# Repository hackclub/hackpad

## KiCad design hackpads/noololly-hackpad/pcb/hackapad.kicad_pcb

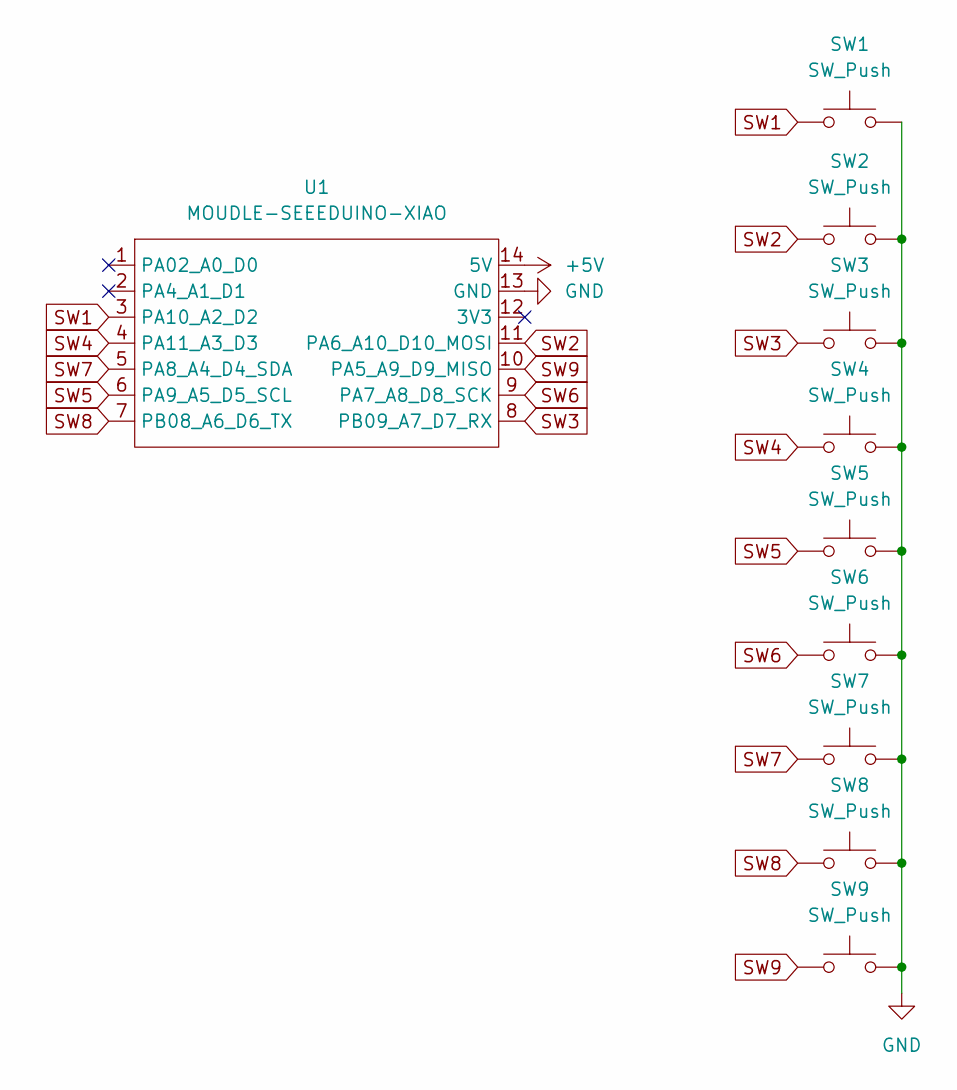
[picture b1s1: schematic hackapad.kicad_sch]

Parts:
SW1, SW2, SW3, SW4, SW5, SW6, SW7, SW8, SW9: SW_Push; SW_Cherry_MX_1.00u_PCB
U1: MOUDLE-SEEEDUINO-XIAO; XIAO-Generic-Hybrid-14P-2.54-21X17.8MM

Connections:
+5V: U1.14 (5V)
GND: SW1.2, SW2.2, SW3.2, SW4.2, SW5.2, SW6.2, SW7.2, SW8.2, SW9.2, U1.13 (GND)
SW1: SW1.1, U1.3 (PA10_A2_D2)
SW2: SW2.1, U1.11 (PA6_A10_D10_MOSI)
SW3: SW3.1, U1.8 (PB09_A7_D7_RX)
SW4: SW4.1, U1.4 (PA11_A3_D3)
SW5: SW5.1, U1.6 (PA9_A5_D5_SCL)
SW6: SW6.1, U1.9 (PA7_A8_D8_SCK)
SW7: SW7.1, U1.5 (PA8_A4_D4_SDA)
SW8: SW8.1, U1.7 (PB08_A6_D6_TX)
SW9: SW9.1, U1.10 (PA5_A9_D9_MISO)

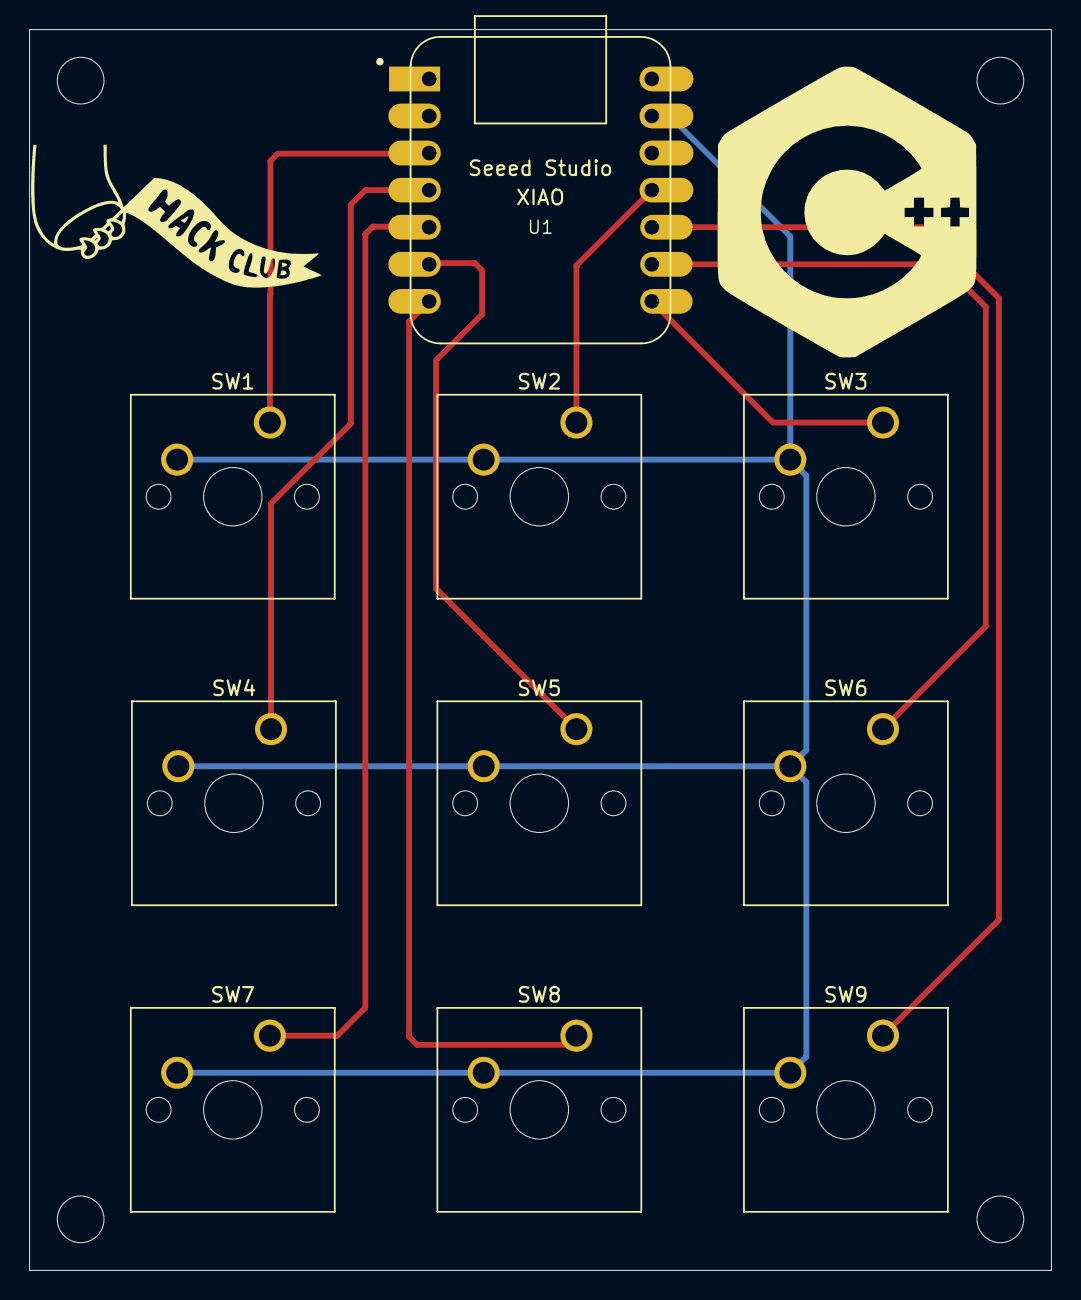
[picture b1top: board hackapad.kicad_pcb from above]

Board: 2 copper layers, 70.0 x 85.0 mm, 10 parts (0 on the bottom side), 10 nets.

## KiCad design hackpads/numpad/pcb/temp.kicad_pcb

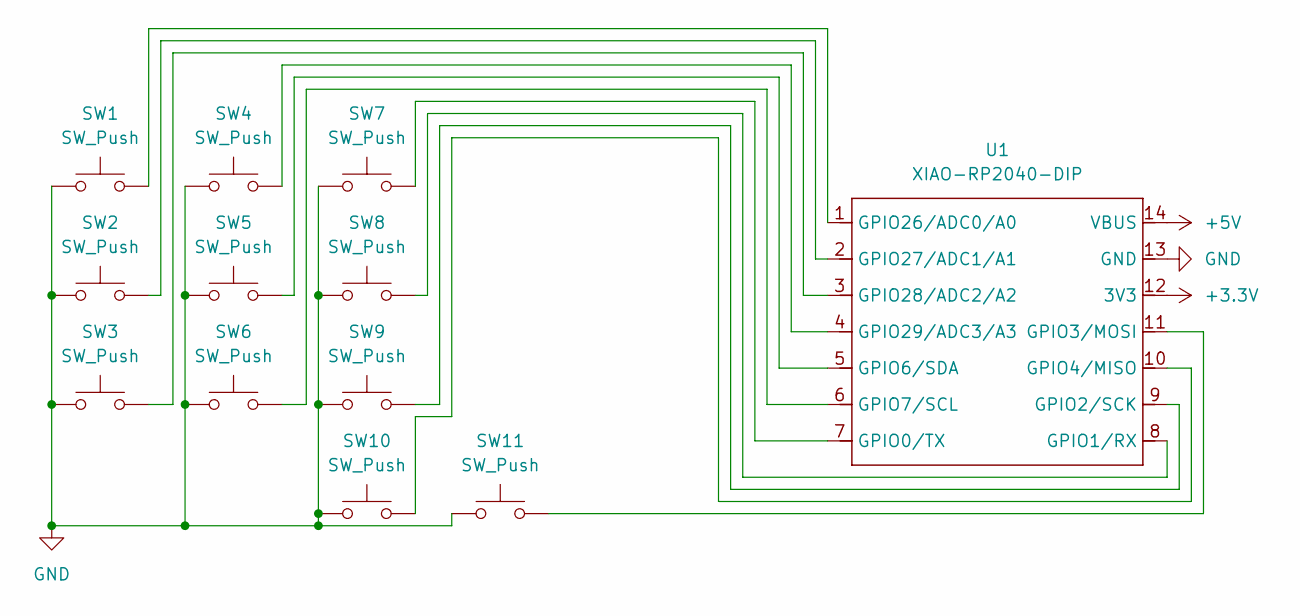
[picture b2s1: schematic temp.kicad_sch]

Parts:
SW1, SW2, SW3, SW4, SW5, SW6, SW7, SW8, SW9, SW10, SW11: SW_Push; SW_Cherry_MX_1.00u_PCB
U1: XIAO-RP2040-DIP

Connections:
+3.3V: U1.12 (3V3)
+5V: U1.14 (VBUS)
GND: SW1.1, SW2.1, SW3.1, SW4.1, SW5.1, SW6.1, SW7.1, SW8.1, SW9.1, SW10.1, SW11.1, U1.13 (GND)
unnamed: SW7.2, U1.7 (GPIO0/TX)
unnamed: SW8.2, U1.8 (GPIO1/RX)
unnamed: SW9.2, U1.9 (GPIO2/SCK)
unnamed: SW11.2, U1.11 (GPIO3/MOSI)
unnamed: SW10.2, U1.10 (GPIO4/MISO)
unnamed: SW5.2, U1.5 (GPIO6/SDA)
unnamed: SW6.2, U1.6 (GPIO7/SCL)
unnamed: SW1.2, U1.1 (GPIO26/ADC0/A0)
unnamed: SW2.2, U1.2 (GPIO27/ADC1/A1)
unnamed: SW3.2, U1.3 (GPIO28/ADC2/A2)
unnamed: SW4.2, U1.4 (GPIO29/ADC3/A3)

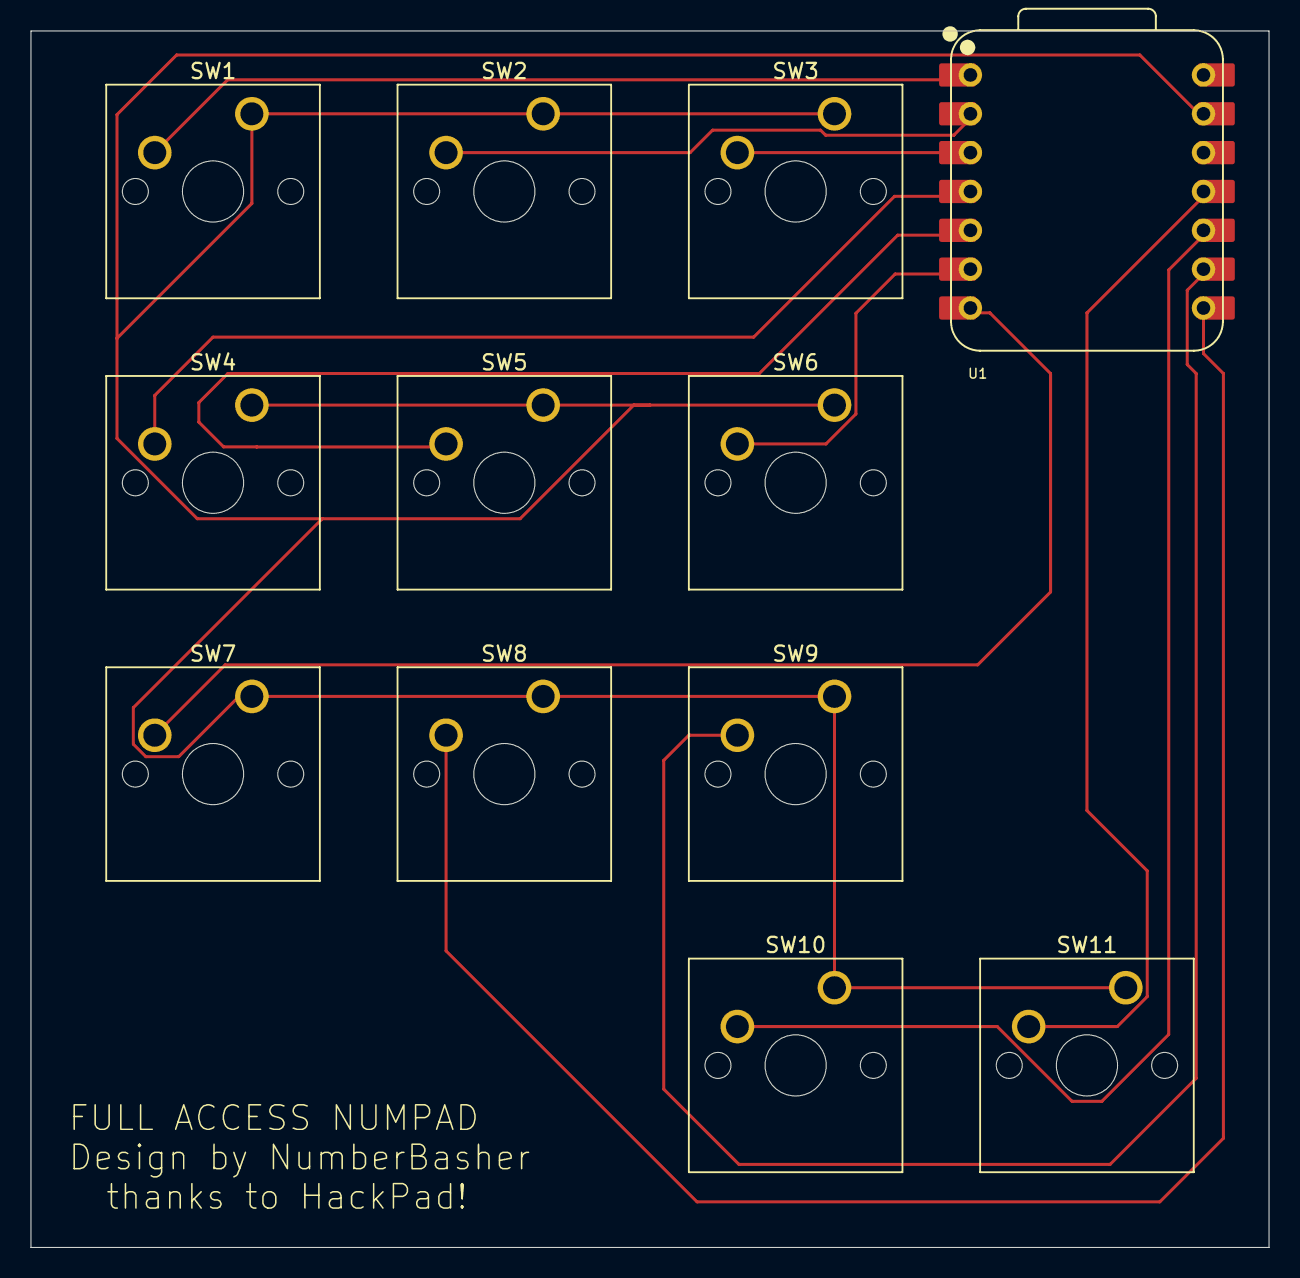
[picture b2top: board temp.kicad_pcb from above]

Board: 2 copper layers, 81.0 x 79.6 mm, 12 parts (0 on the bottom side), 12 nets.

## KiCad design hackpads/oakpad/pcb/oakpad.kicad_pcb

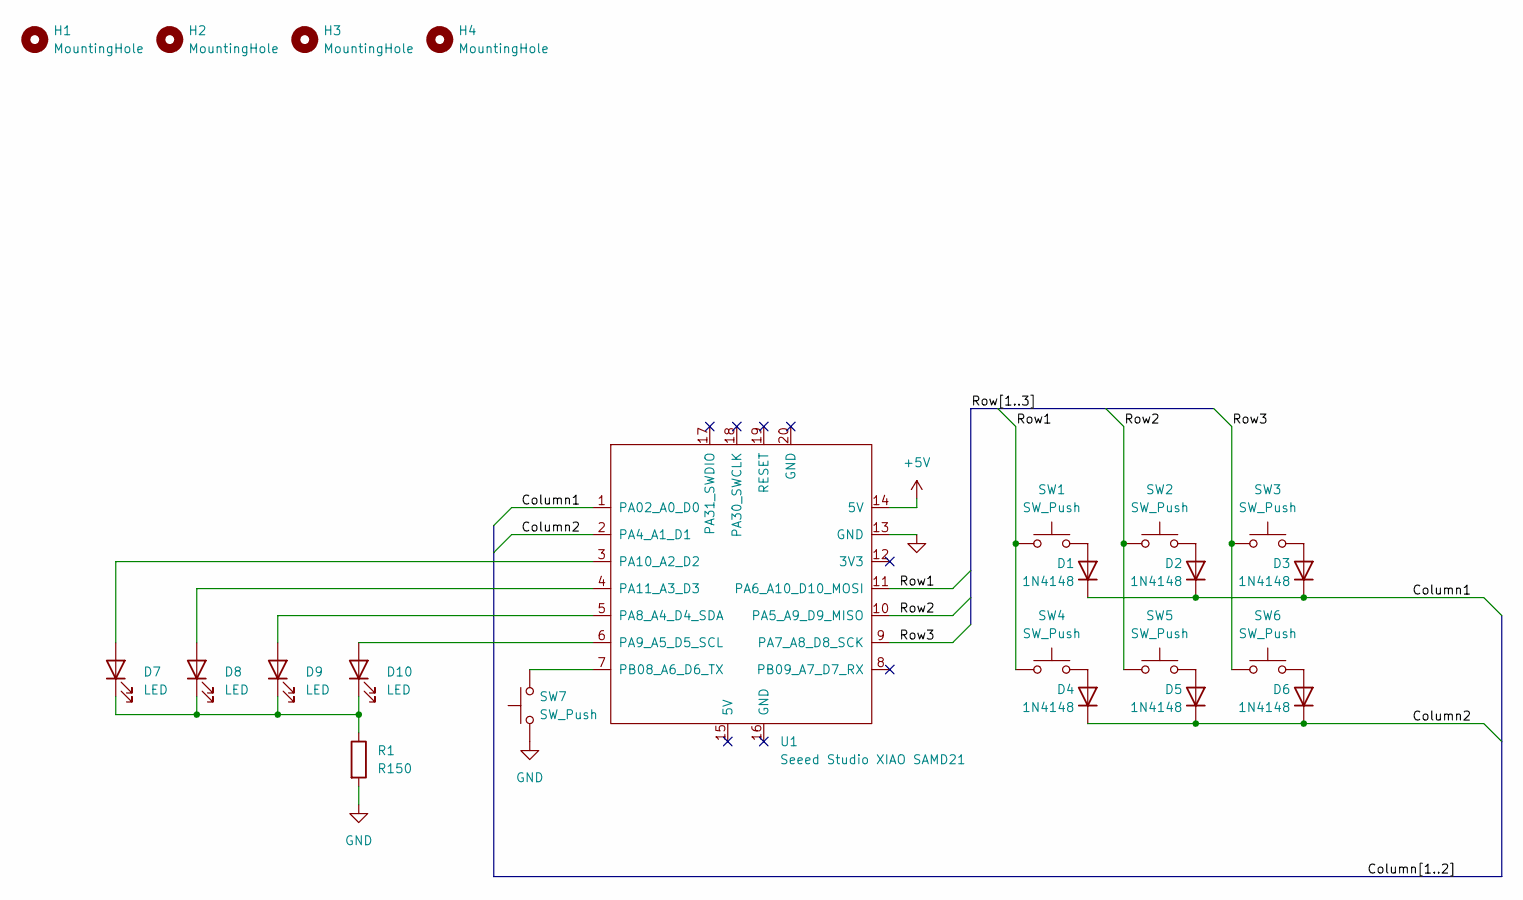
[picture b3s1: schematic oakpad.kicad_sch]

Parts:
D1, D2, D3, D4, D5, D6: 1N4148; D_DO-35_SOD27_P7.62mm_Horizontal
D7, D8, D9, D10: LED; LED_D5.0mm
H1, H2, H3, H4: MountingHole; MountingHole_3.2mm_M3
R1: R150; R_Axial_DIN0204_L3.6mm_D1.6mm_P5.08mm_Horizontal
SW1, SW2, SW3, SW4, SW5, SW6, SW7: SW_Push; SW_Cherry_MX_1.00u_PCB
U1: Seeed Studio XIAO SAMD21; XIAO-Generic-Thruhole-14P-2.54-21X17.8MM

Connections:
+5V: U1.14 (5V)
/Column1: D1.1 (K), D2.1 (K), D3.1 (K), U1.1 (PA02_A0_D0)
/Column2: D4.1 (K), D5.1 (K), D6.1 (K), U1.2 (PA4_A1_D1)
/Row1: SW1.1, SW4.1, U1.11 (PA6_A10_D10_MOSI)
/Row2: SW2.1, SW5.1, U1.10 (PA5_A9_D9_MISO)
/Row3: SW3.1, SW6.1, U1.9 (PA7_A8_D8_SCK)
GND: R1.2, SW7.1, U1.13 (GND)
unnamed: D1.2 (A), SW1.2
unnamed: D2.2 (A), SW2.2
unnamed: D3.2 (A), SW3.2
unnamed: D4.2 (A), SW4.2
unnamed: D5.2 (A), SW5.2
unnamed: D6.2 (A), SW6.2
unnamed: D7.2 (A), U1.3 (PA10_A2_D2)
unnamed: D8.2 (A), U1.4 (PA11_A3_D3)
unnamed: D9.2 (A), U1.5 (PA8_A4_D4_SDA)
unnamed: D10.2 (A), U1.6 (PA9_A5_D5_SCL)
unnamed: D7.1 (K), D8.1 (K), D9.1 (K), D10.1 (K), R1.1
unnamed: SW7.2, U1.7 (PB08_A6_D6_TX)

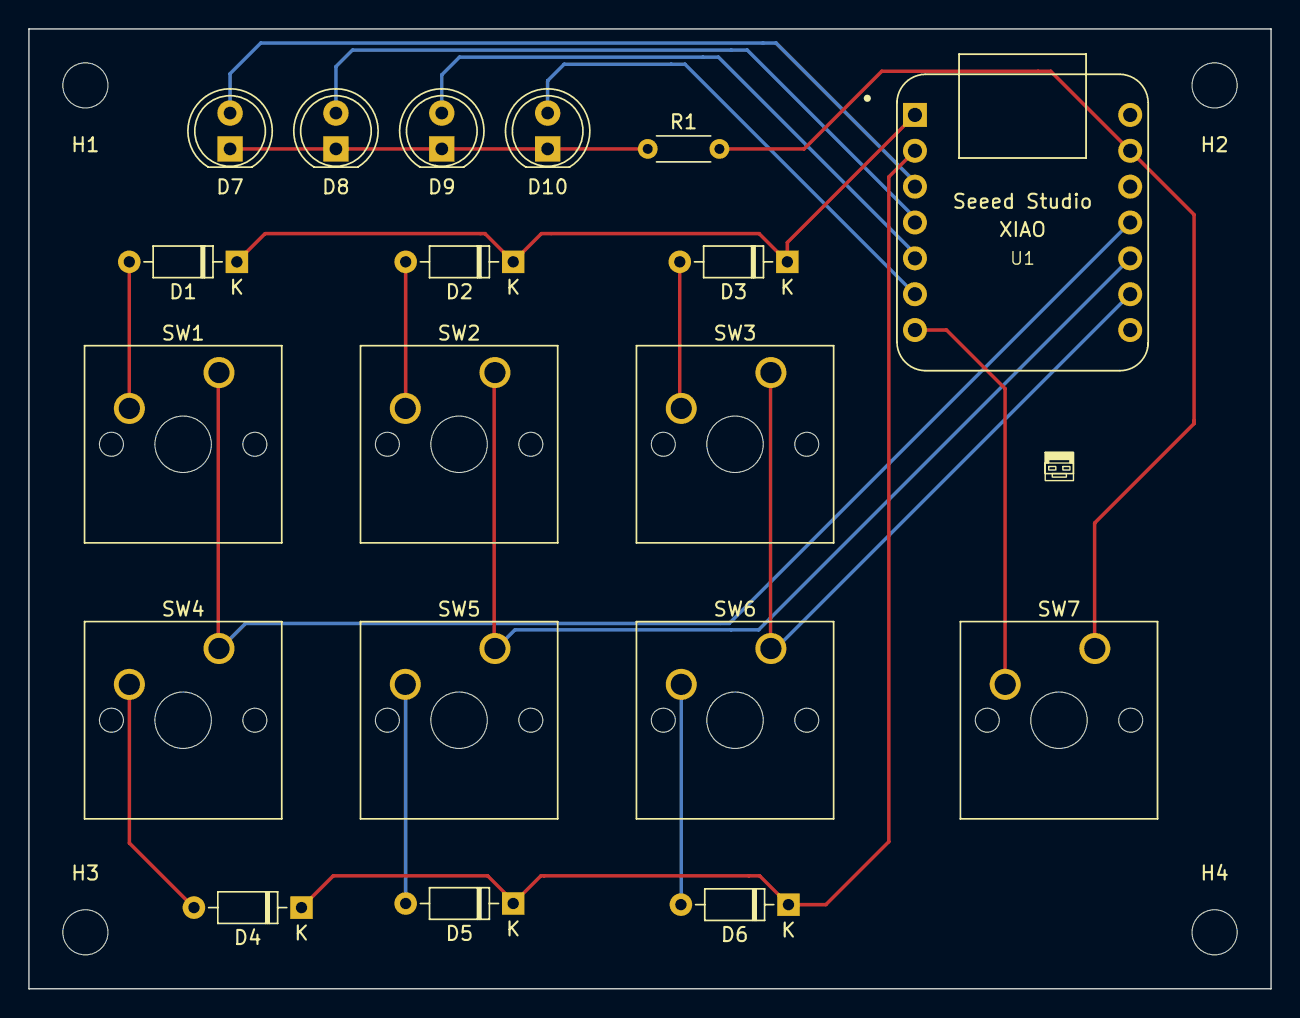
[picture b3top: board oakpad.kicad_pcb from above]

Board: 2 copper layers, 88.0 x 68.0 mm, 23 parts (0 on the bottom side), 18 nets.

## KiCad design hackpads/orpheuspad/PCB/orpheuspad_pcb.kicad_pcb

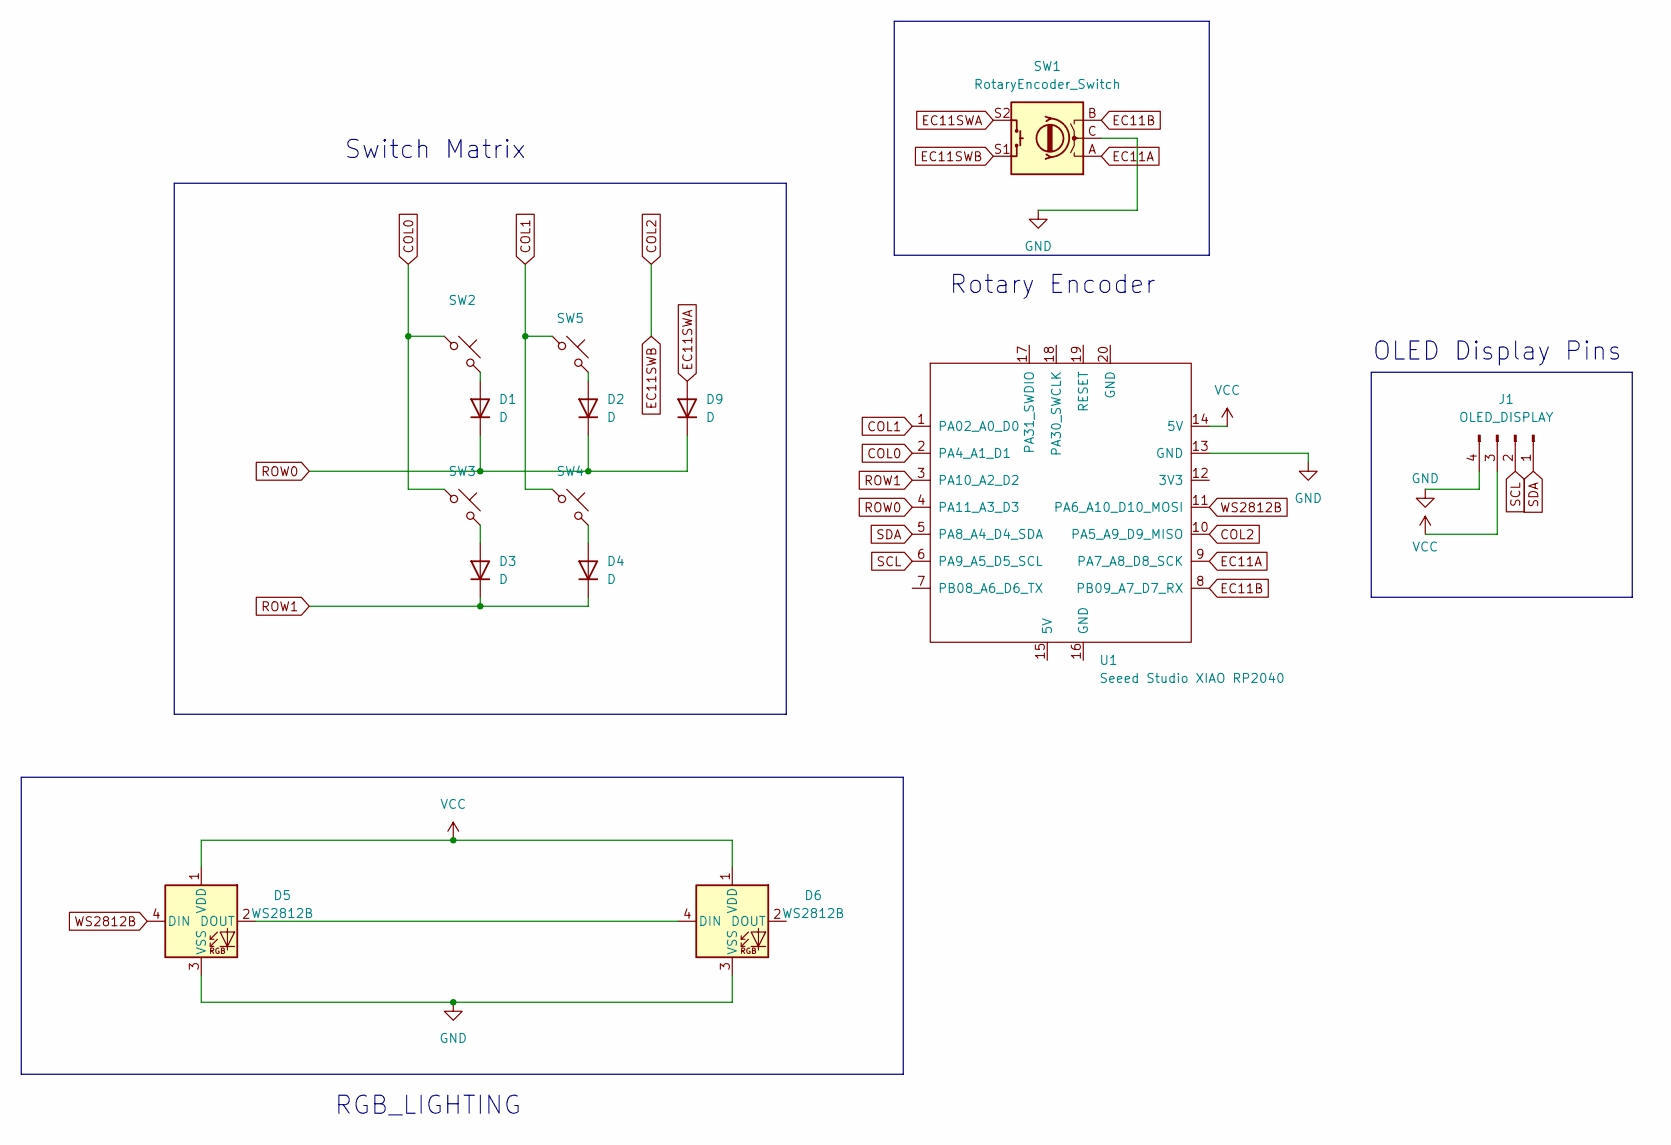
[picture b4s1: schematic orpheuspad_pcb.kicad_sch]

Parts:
D1, D2, D3, D4, D9: D; D_DO-35_SOD27_P7.62mm_Horizontal
D5, D6: WS2812B; LED_WS2812B_PLCC4_5.0x5.0mm_P3.2mm
J1: OLED_DISPLAY; PinHeader_1x04_P2.54mm_Vertical
SW1: RotaryEncoder_Switch; RotaryEncoder_Alps_EC11E-Switch_Vertical_H20mm
SW2, SW3, SW4, SW5: SW_Push_45deg; MX-Solderable-1U
U1: Seeed Studio XIAO RP2040; XIAO-Generic-Hybrid-14P-2.54-21X17.8MM

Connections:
COL0: SW2.1, SW3.1, U1.2 (PA4_A1_D1)
COL1: SW4.1, SW5.1, U1.1 (PA02_A0_D0)
COL2: SW1.S1, U1.10 (PA5_A9_D9_MISO); also elsewhere on the board
EC11A: SW1.A, U1.9 (PA7_A8_D8_SCK); also elsewhere on the board
EC11B: SW1.B, U1.8 (PB09_A7_D7_RX); also elsewhere on the board
EC11SWA: D9.2 (A), SW1.S2; also elsewhere on the board
GND: D5.3 (VSS), D6.3 (VSS), J1.4, SW1.C, U1.13 (GND); also elsewhere on the board
unnamed: D1.2 (A), SW2.2
unnamed: D2.2 (A), SW5.2
unnamed: D3.2 (A), SW3.2
unnamed: D4.2 (A), SW4.2
unnamed: D5.2 (DOUT), D6.4 (DIN)
ROW0: D1.1 (K), D2.1 (K), D9.1 (K), U1.4 (PA11_A3_D3)
ROW1: D3.1 (K), D4.1 (K), U1.3 (PA10_A2_D2)
SCL: J1.2, U1.6 (PA9_A5_D5_SCL)
SDA: J1.1, U1.5 (PA8_A4_D4_SDA)
VCC: D5.1 (VDD), D6.1 (VDD), J1.3, U1.14 (5V)
WS2812B: D5.4 (DIN), U1.11 (PA6_A10_D10_MOSI)

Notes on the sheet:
RGB_LIGHTING
Switch Matrix
Rotary Encoder
OLED Display Pins

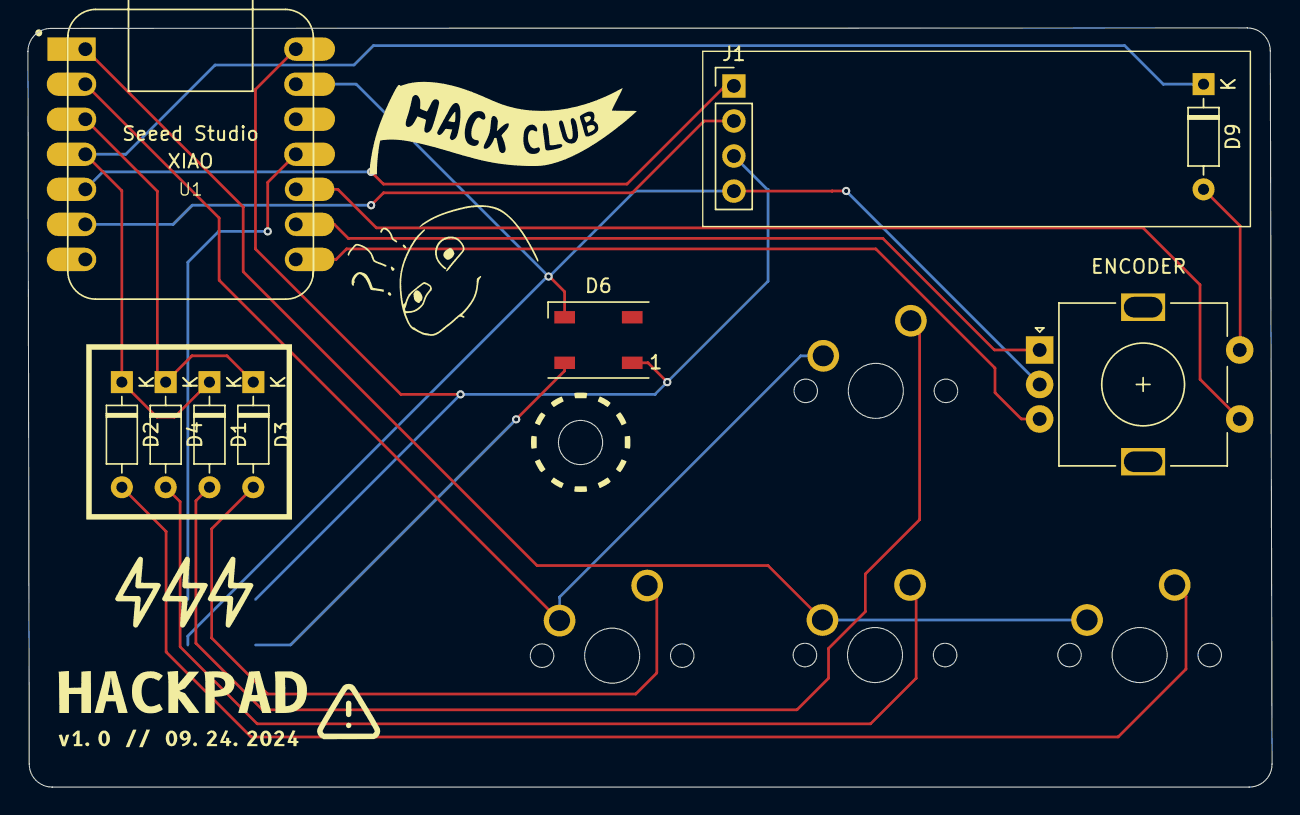
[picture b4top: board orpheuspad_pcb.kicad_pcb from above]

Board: 2 copper layers, 90.2 x 55.0 mm, 14 parts (1 on the bottom side), 18 nets.

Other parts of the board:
ENCODER: RotaryEncoder_Switch; RotaryEncoder_Alps_EC11E-Switch_Vertical_H20mm

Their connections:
COL2: ENCODER.S1; also elsewhere on the board
EC11A: ENCODER.A; also elsewhere on the board
EC11B: ENCODER.B; also elsewhere on the board
EC11SWA: ENCODER.S2; also elsewhere on the board
GND: ENCODER.C; also elsewhere on the board

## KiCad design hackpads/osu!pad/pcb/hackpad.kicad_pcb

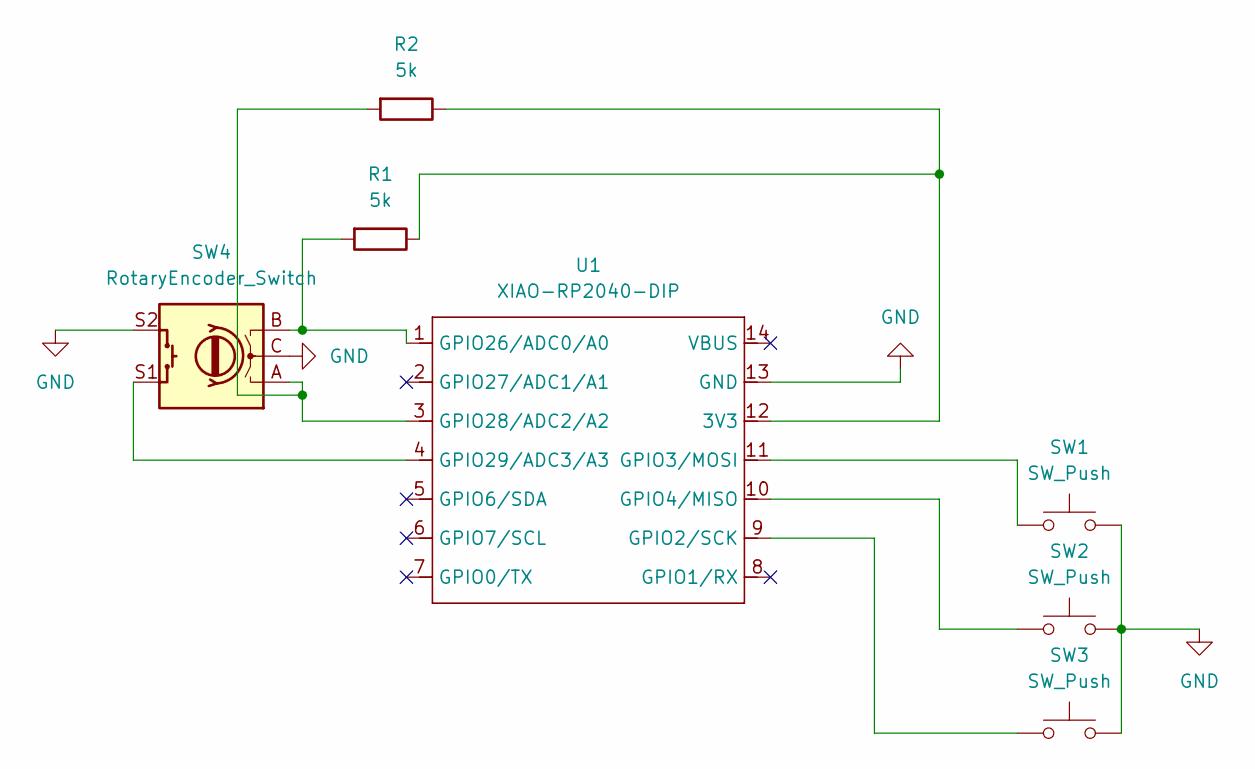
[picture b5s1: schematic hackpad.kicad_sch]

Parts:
R1, R2: 5k; R_Axial_DIN0204_L3.6mm_D1.6mm_P7.62mm_Horizontal
SW1, SW2, SW3: SW_Push; SW_Cherry_MX_1.00u_PCB
SW4: RotaryEncoder_Switch; RotaryEncoder_Alps_EC11E-Switch_Vertical_H20mm_CircularMoun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
U1: XIAO-RP2040-DIP

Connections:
GND: SW1.2, SW2.2, SW3.2, SW4.C, SW4.S2, U1.13 (GND)
unnamed: R1.1, R2.1, U1.12 (3V3)
unnamed: SW3.1, U1.9 (GPIO2/SCK)
unnamed: SW1.1, U1.11 (GPIO3/MOSI)
unnamed: SW2.1, U1.10 (GPIO4/MISO)
unnamed: R1.2, SW4.B, U1.1 (GPIO26/ADC0/A0)
unnamed: R2.2, SW4.A, U1.3 (GPIO28/ADC2/A2)
unnamed: SW4.S1, U1.4 (GPIO29/ADC3/A3)

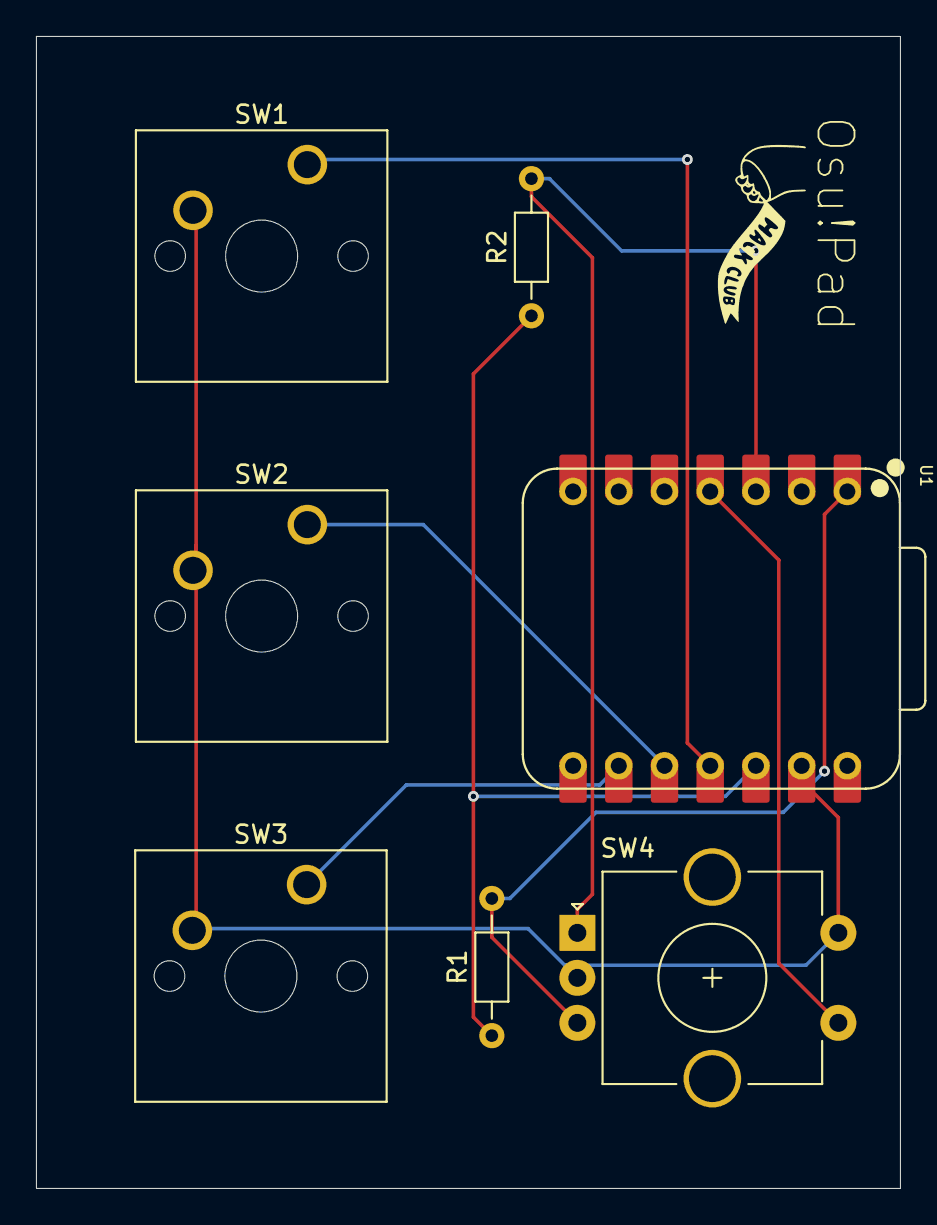
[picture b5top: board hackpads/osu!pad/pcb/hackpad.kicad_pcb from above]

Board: 2 copper layers, 48.0 x 64.0 mm, 7 parts (0 on the bottom side), 8 nets.

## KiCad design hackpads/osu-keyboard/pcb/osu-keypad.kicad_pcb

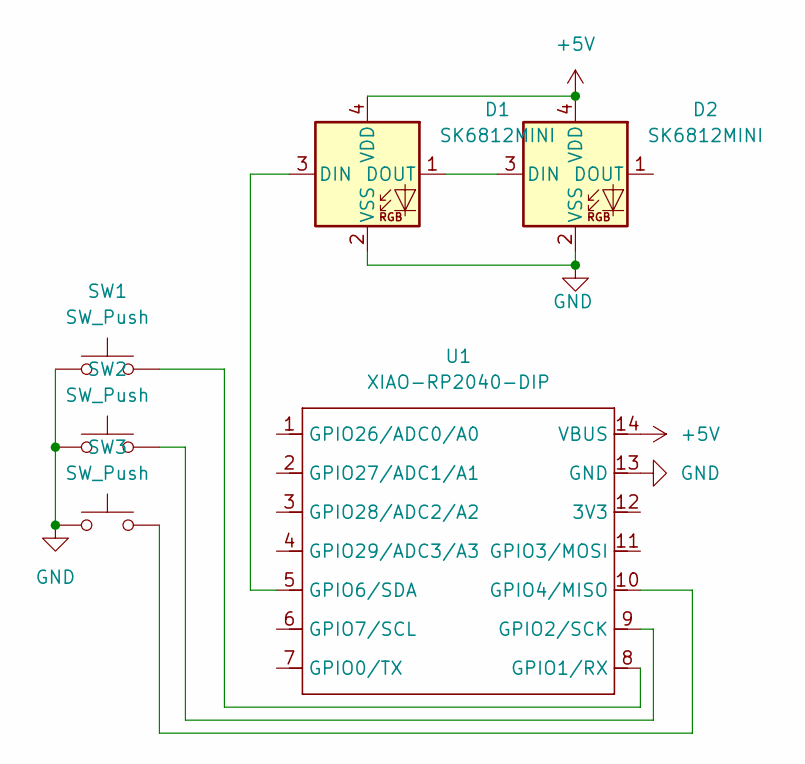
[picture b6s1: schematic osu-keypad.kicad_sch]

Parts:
D1, D2: SK6812MINI; LED_SK6812MINI_PLCC4_3.5x3.5mm_P1.75mm
SW1, SW2, SW3: SW_Push; SW_Cherry_MX_1.00u_PCB
U1: XIAO-RP2040-DIP

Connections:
+5V: D1.4 (VDD), D2.4 (VDD), U1.14 (VBUS)
GND: D1.2 (VSS), D2.2 (VSS), SW1.1, SW2.1, SW3.1, U1.13 (GND)
unnamed: D1.3 (DIN), U1.5 (GPIO6/SDA)
unnamed: D1.1 (DOUT), D2.3 (DIN)
unnamed: SW1.2, U1.8 (GPIO1/RX)
unnamed: SW2.2, U1.9 (GPIO2/SCK)
unnamed: SW3.2, U1.10 (GPIO4/MISO)

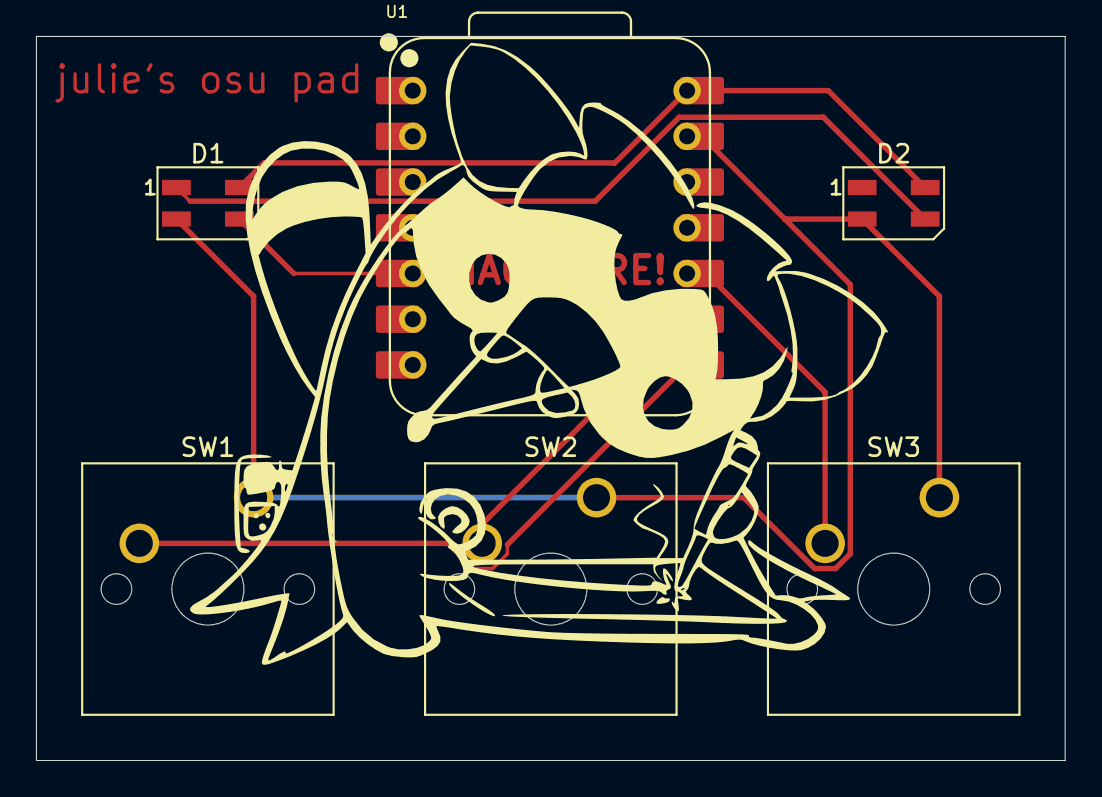
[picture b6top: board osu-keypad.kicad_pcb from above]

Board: 2 copper layers, 57.2 x 40.2 mm, 6 parts (0 on the bottom side), 7 nets.

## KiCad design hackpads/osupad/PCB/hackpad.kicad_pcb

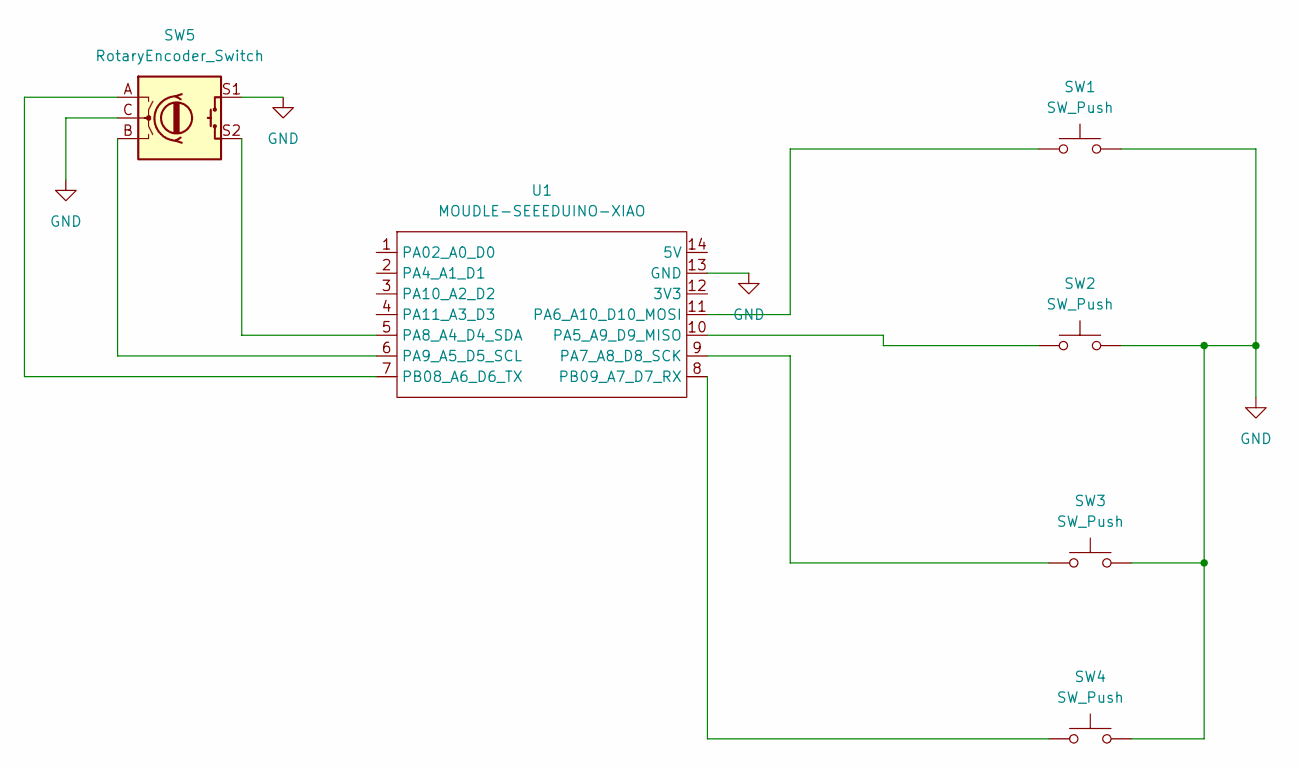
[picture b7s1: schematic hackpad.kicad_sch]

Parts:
SW1, SW2, SW3, SW4: SW_Push; SW_Cherry_MX_1.00u_PCB
SW5: RotaryEncoder_Switch; RotaryEncoder_Alps_EC11E-Switch_Vertical_H20mm
U1: MOUDLE-SEEEDUINO-XIAO; XIAO-Generic-Hybrid-14P-2.54-21X17.8MM

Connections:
GND: SW1.2, SW2.2, SW3.2, SW4.2, SW5.C, SW5.S1, U1.13 (GND)
unnamed: SW2.1, U1.10 (PA5_A9_D9_MISO)
unnamed: SW1.1, U1.11 (PA6_A10_D10_MOSI)
unnamed: SW3.1, U1.9 (PA7_A8_D8_SCK)
unnamed: SW5.S2, U1.5 (PA8_A4_D4_SDA)
unnamed: SW5.B, U1.6 (PA9_A5_D5_SCL)
unnamed: SW5.A, U1.7 (PB08_A6_D6_TX)
unnamed: SW4.1, U1.8 (PB09_A7_D7_RX)

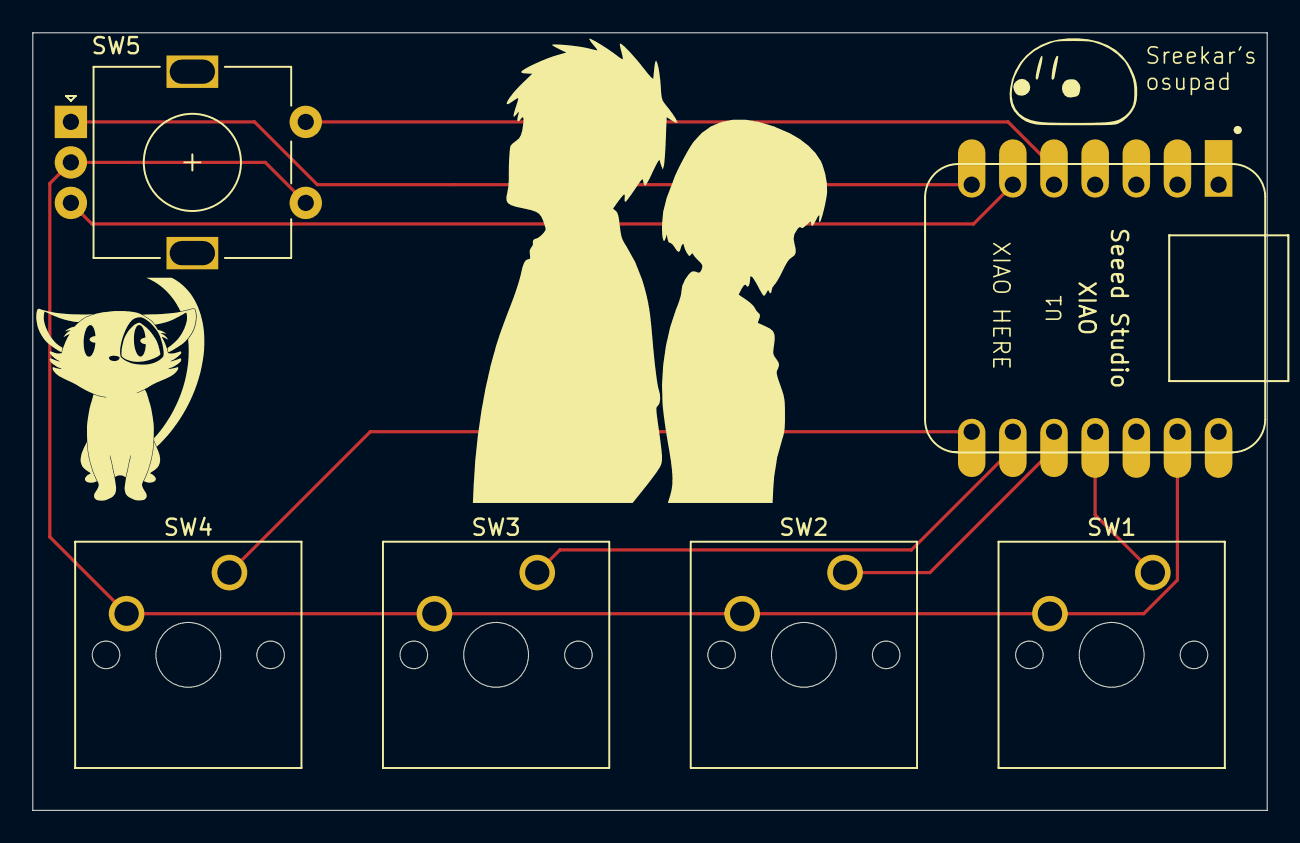
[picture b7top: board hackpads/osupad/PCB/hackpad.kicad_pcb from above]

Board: 2 copper layers, 76.2 x 48.0 mm, 6 parts (0 on the bottom side), 8 nets.

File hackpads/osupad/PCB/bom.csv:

"Id";"Designator";"Footprint";"Quantity";"Designation";"Supplier and ref";
1;"SW3,SW4,SW2,SW1";"SW_Cherry_MX_1.00u_PCB";4;"SW_Push";;;
2;"U1";"XIAO-Generic-Hybrid-14P-2.54-21X17.8MM";1;"MOUDLE-SEEEDUINO-XIAO";;;
3;"SW5";"RotaryEncoder_Alps_EC11E-Switch_Vertical_H20mm";1;"RotaryEncoder_Switch";;;
